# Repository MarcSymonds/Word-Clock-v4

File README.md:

# Word-Clock-v4
Version 4 of my Word Clock. Now uses an Arduino and WS2812 RGB LEDs.

My original Word Clock used a PICAXE microcontroller and plain white LEDs to show the time.

This version is a complete redesign and uses and Arduino Nano and WS2812B RGD LEDs to show the time in various colours.

To hold the LEDs, I used Wings3D to create a 11x5 frame to hold 55 LEDs (the clock uses 110 LEDs), and printed that on a 3D printer.

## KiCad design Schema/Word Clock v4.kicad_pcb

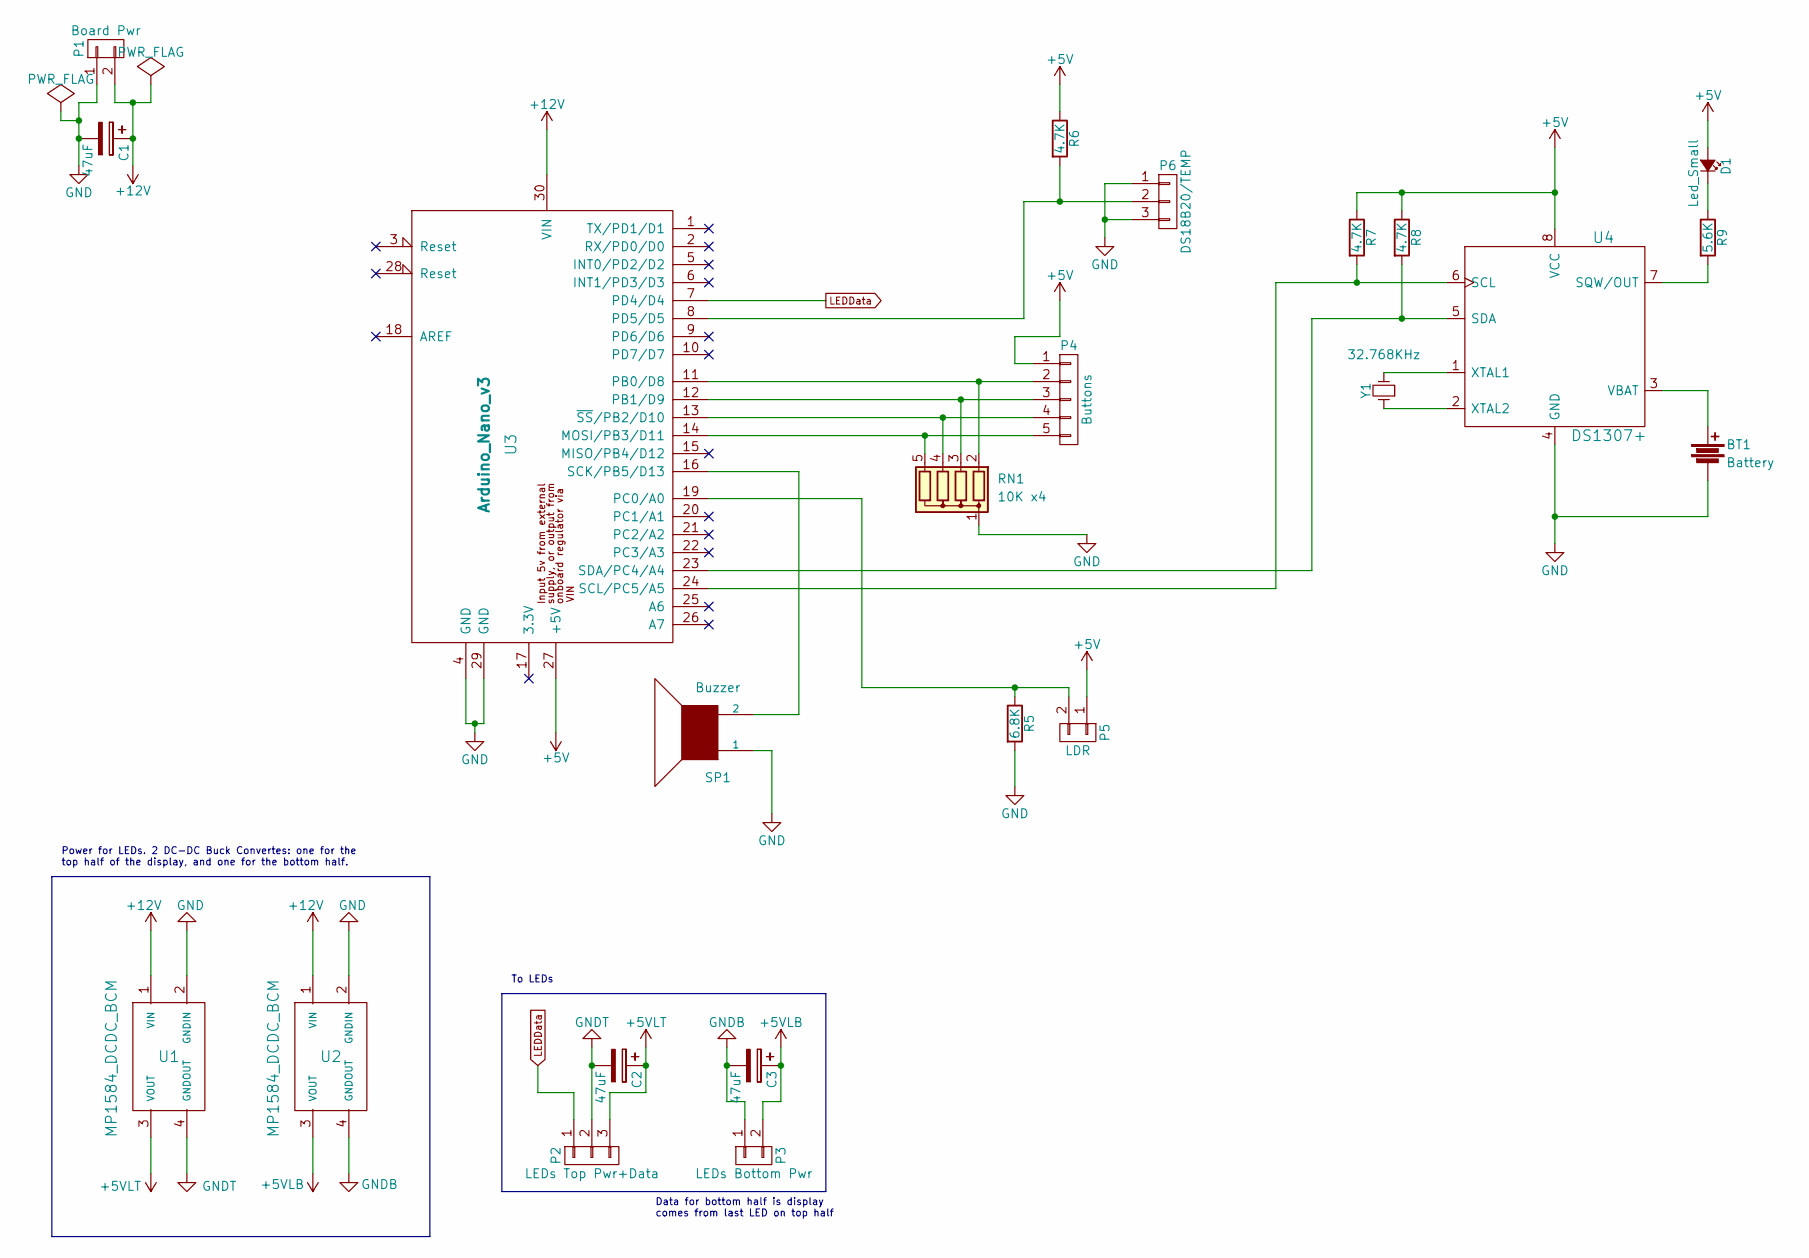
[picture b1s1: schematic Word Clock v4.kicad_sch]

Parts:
BT1: Battery; keystone_1025-7
C1, C2, C3: 47uF; CP_Radial_D7.5mm_P2.50mm
D1: Led_Small; LED_D5.0mm_Horizontal_O6.35mm_Z3.0mm
P1: Board Pwr; Pin_Header_Angled_1x02
P2: LEDs Top Pwr+Data; Pin_Header_Angled_1x03
P3: LEDs Bottom Pwr; Pin_Header_Angled_1x02
P4: Buttons; Pin_Header_Angled_1x05
P5: LDR; Pin_Header_Angled_1x02
P6: DS18B20/TEMP; Pin_Header_Angled_1x03
R5: 6.8K; Resistor_Horizontal_RM10mm
R6, R7, R8: 4.7K; Resistor_Horizontal_RM10mm
R9: 5.6K; Resistor_Horizontal_RM10mm
RN1: 10K x4; R_Array_SIP5
SP1: Buzzer; Pin_Header_Angled_1x02
U1, U2: MP1584_DCDC_BCM
U3: Arduino_Nano_v3
U4: DS1307+; DIP-8_W7.62mm_LongPads
Y1: 32.768KHz; Crystal_Round_Horizontal_3mm_BigPad

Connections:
+5V: D1.1 (A), P4.1, P5.1, R6.1, R7.1, R8.1, U3.27 (+5V), U4.8 (VCC)
+5VLB: C3.1, P3.2, U2.3 (VOUT)
+5VLT: C2.1, P2.3, U1.3 (VOUT)
+12V: C1.1, P1.2, U1.1 (VIN), U2.1 (VIN), U3.30 (VIN)
GND: BT1.2, C1.2, P1.1, P6.1, P6.3, R5.2, RN1.1 (common), SP1.1, U1.2 (GNDIN), U2.2 (GNDIN), U3.4 (GND), U3.29 (GND), U4.4 (GND)
GNDB: C3.2, P3.1, U2.4 (GNDOUT)
GNDT: C2.2, P2.2, U1.4 (GNDOUT)
LEDData: P2.1, U3.7 (PD4/D4)
unnamed: D1.2 (C), R9.1
unnamed: P4.2, RN1.2 (R1), U3.11 (PB0/D8)
unnamed: P4.3, RN1.3 (R2), U3.12 (PB1/D9)
unnamed: P4.4, RN1.4 (R3), U3.13 (~SS/PB2/D10)
unnamed: P4.5, RN1.5 (R4), U3.14 (MOSI/PB3/D11)
unnamed: P5.2, R5.1, U3.19 (PC0/A0)
unnamed: P6.2, R6.2, U3.8 (PD5/D5)
unnamed: SP1.2, U3.16 (SCK/PB5/D13)
unnamed: R7.2, U3.24 (SCL/PC5/A5), U4.6 (SCL)
unnamed: R8.2, U3.23 (SDA/PC4/A4), U4.5 (SDA)
unnamed: R9.2, U4.7 (SQW/OUT)
unnamed: BT1.1, U4.3 (VBAT)
unnamed: U4.1 (XTAL1), Y1.2
unnamed: U4.2 (XTAL2), Y1.1

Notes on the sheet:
Power for LEDs. 2 DC-DC Buck Convertes: one for the top half of the display, and one for the bottom half.
Data for bottom half is display comes from last LED on top half
To LEDs

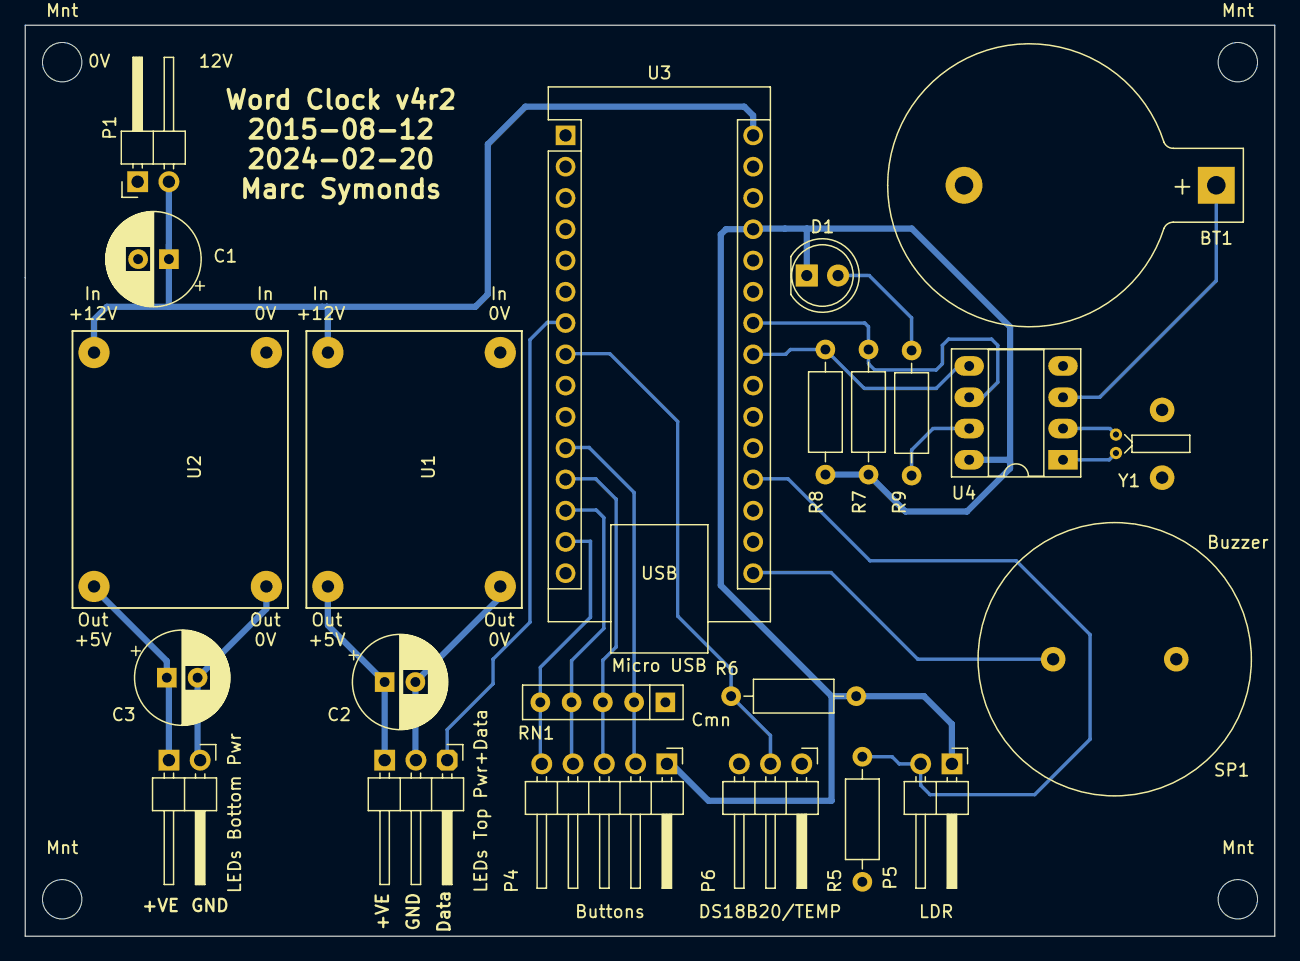
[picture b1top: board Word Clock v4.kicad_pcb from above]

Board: 2 copper layers, 101.5 x 74.0 mm, 27 parts (0 on the bottom side), 22 nets.

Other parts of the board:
Mnt: MountingHole_3.2mm_M3
Mnt#2, Mnt#3, Mnt#4: MountingHole_3.2mm_M3

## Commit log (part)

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2017-03-24 Images for README.
